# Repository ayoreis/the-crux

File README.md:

# The Crux

A minimal 3x10 ortholinear keyboard. Driven by a RP2040 with [RMK](https://rmk.rs) + [Vial](https://get.vial.today).

I've always wanted to make a keyboard, I actually started this one with much more ambitious ideas (you can find them in my earlier journals, or by going back the commit history) but realized I should start out with something simpler. So I made this! It was quite nice, and maybe I'll improve it with my previous ideas one-by-one :)

# File structure and assembly

At the top-level there's a general "bom.csv". Then the directories:

- "pcb/" contains a KiCad project and generated production files with KiCAD JLCPCB tools under "pcb/jlcpcb/".
- "case/" contains a FreeCAD file and an exported "case.step".
- "images/" contains the images above and the zine in PDF format.
- "firmware/" contains the RMK and Vial firmware. With the compiled UF2 file at "firmware/The_Crux.uf2".

The case and plate are a single piece sandwiched between the switches and PCB, so it must be fit before soldering.

---

_[Also see this project on Fallout.](https://fallout.hackclub.com/projects/4383)_

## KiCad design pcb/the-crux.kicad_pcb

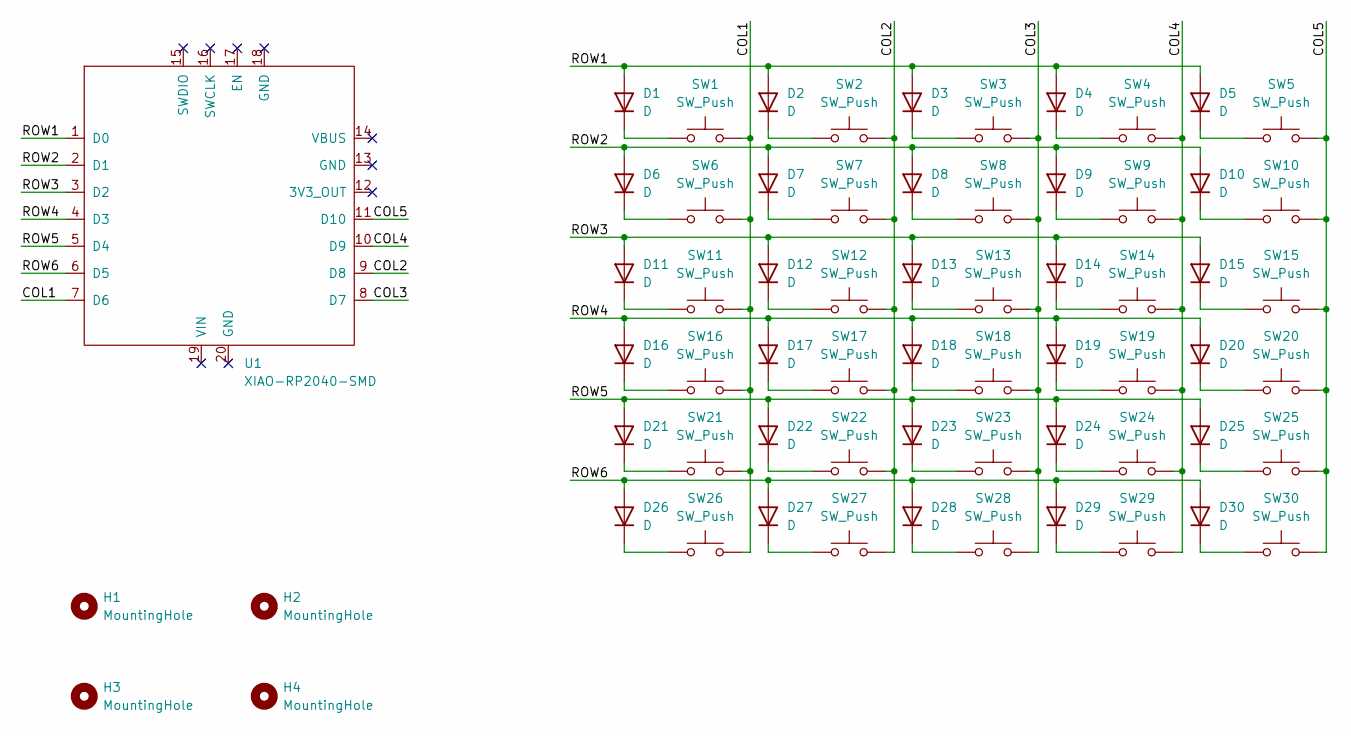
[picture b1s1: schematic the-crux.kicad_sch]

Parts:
D1, D2, D3, D4, D5, D6, D7, D8, D9, D10, D11, D12, D13, D14, D15, D16, D17, D18, D19, D20, D21, D22, D23, D24, D25, D26, D27, D28, D29, D30: D; D_DO-35_SOD27_P7.62mm_Horizontal
H1, H2, H3, H4: MountingHole; MountingHole_2.2mm_M2_Pad
SW1, SW2, SW3, SW4, SW5, SW6, SW7, SW8, SW9, SW10, SW11, SW12, SW13, SW14, SW15, SW16, SW17, SW18, SW19, SW20, SW21, SW22, SW23, SW24, SW25, SW26, SW27, SW28, SW29, SW30: SW_Push; SW_Cherry_MX_1.00u_PCB
U1: XIAO-RP2040-SMD

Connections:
/COL1: SW1.2, SW6.2, SW11.2, SW16.2, SW21.2, SW26.2, U1.7 (D6)
/COL2: SW2.2, SW7.2, SW12.2, SW17.2, SW22.2, SW27.2, U1.9 (D8)
/COL3: SW3.2, SW8.2, SW13.2, SW18.2, SW23.2, SW28.2, U1.8 (D7)
/COL4: SW4.2, SW9.2, SW14.2, SW19.2, SW24.2, SW29.2, U1.10 (D9)
/COL5: SW5.2, SW10.2, SW15.2, SW20.2, SW25.2, SW30.2, U1.11 (D10)
/ROW1: D1.2 (A), D2.2 (A), D3.2 (A), D4.2 (A), D5.2 (A), U1.1 (D0)
/ROW2: D6.2 (A), D7.2 (A), D8.2 (A), D9.2 (A), D10.2 (A), U1.2 (D1)
/ROW3: D11.2 (A), D12.2 (A), D13.2 (A), D14.2 (A), D15.2 (A), U1.3 (D2)
/ROW4: D16.2 (A), D17.2 (A), D18.2 (A), D19.2 (A), D20.2 (A), U1.4 (D3)
/ROW5: D21.2 (A), D22.2 (A), D23.2 (A), D24.2 (A), D25.2 (A), U1.5 (D4)
/ROW6: D26.2 (A), D27.2 (A), D28.2 (A), D29.2 (A), D30.2 (A), U1.6 (D5)
unnamed: D1.1 (K), SW1.1
unnamed: D2.1 (K), SW2.1
unnamed: D3.1 (K), SW3.1
unnamed: D4.1 (K), SW4.1
unnamed: D5.1 (K), SW5.1
unnamed: D6.1 (K), SW6.1
unnamed: D7.1 (K), SW7.1
unnamed: D8.1 (K), SW8.1
unnamed: D9.1 (K), SW9.1
unnamed: D10.1 (K), SW10.1
unnamed: D11.1 (K), SW11.1
unnamed: D12.1 (K), SW12.1
unnamed: D13.1 (K), SW13.1
unnamed: D14.1 (K), SW14.1
unnamed: D15.1 (K), SW15.1
unnamed: D16.1 (K), SW16.1
unnamed: D17.1 (K), SW17.1
unnamed: D18.1 (K), SW18.1
unnamed: D19.1 (K), SW19.1
unnamed: D20.1 (K), SW20.1
unnamed: D21.1 (K), SW21.1
unnamed: D22.1 (K), SW22.1
unnamed: D23.1 (K), SW23.1
unnamed: D24.1 (K), SW24.1
unnamed: D25.1 (K), SW25.1
unnamed: D26.1 (K), SW26.1
unnamed: D27.1 (K), SW27.1
unnamed: D28.1 (K), SW28.1
unnamed: D29.1 (K), SW29.1
unnamed: D30.1 (K), SW30.1

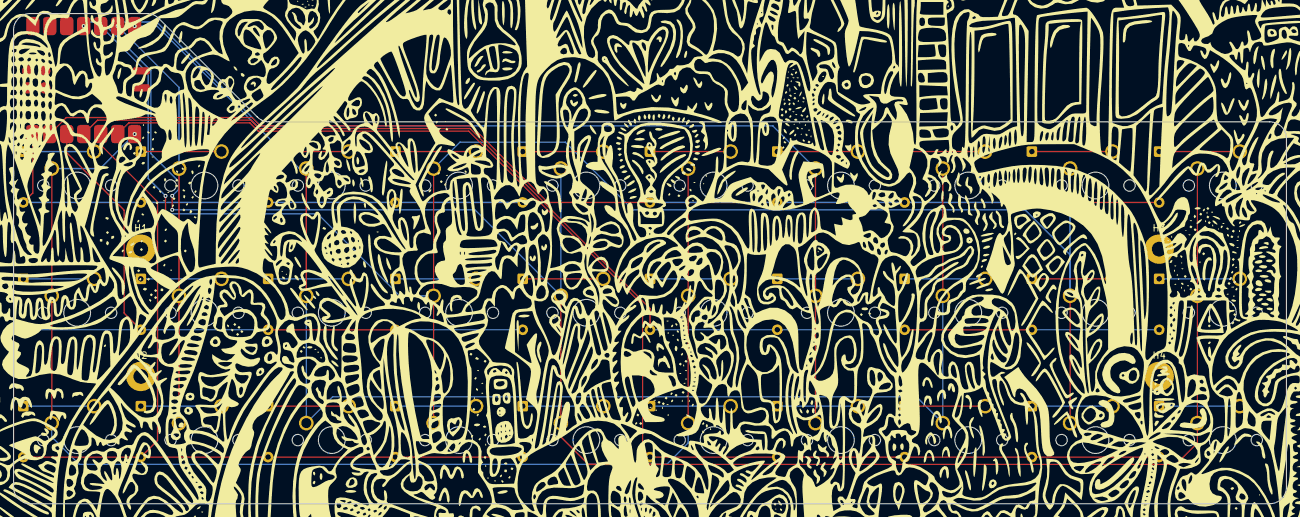
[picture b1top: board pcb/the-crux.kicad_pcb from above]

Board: 2 copper layers, 190.5 x 73.4 mm, 65 parts (0 on the bottom side), 41 nets.

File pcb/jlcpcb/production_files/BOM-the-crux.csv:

Comment,Designator,Footprint,LCSC,Quantity
XIAO-RP2040-SMD,U1,XIAO-RP2040-SMD,,1
SW_Push,SW30,SW_Cherry_MX_1.00u_PCB,,1
SW_Push,SW29,SW_Cherry_MX_1.00u_PCB,,1
SW_Push,SW28,SW_Cherry_MX_1.00u_PCB,,1
SW_Push,SW27,SW_Cherry_MX_1.00u_PCB,,1
SW_Push,SW26,SW_Cherry_MX_1.00u_PCB,,1
SW_Push,SW25,SW_Cherry_MX_1.00u_PCB,,1
SW_Push,SW24,SW_Cherry_MX_1.00u_PCB,,1
SW_Push,SW23,SW_Cherry_MX_1.00u_PCB,,1
SW_Push,SW22,SW_Cherry_MX_1.00u_PCB,,1
SW_Push,SW21,SW_Cherry_MX_1.00u_PCB,,1
SW_Push,SW20,SW_Cherry_MX_1.00u_PCB,,1
SW_Push,SW19,SW_Cherry_MX_1.00u_PCB,,1
SW_Push,SW18,SW_Cherry_MX_1.00u_PCB,,1
SW_Push,SW17,SW_Cherry_MX_1.00u_PCB,,1
SW_Push,SW16,SW_Cherry_MX_1.00u_PCB,,1
SW_Push,SW15,SW_Cherry_MX_1.00u_PCB,,1
SW_Push,SW14,SW_Cherry_MX_1.00u_PCB,,1
SW_Push,SW13,SW_Cherry_MX_1.00u_PCB,,1
SW_Push,SW12,SW_Cherry_MX_1.00u_PCB,,1
SW_Push,SW11,SW_Cherry_MX_1.00u_PCB,,1
SW_Push,SW10,SW_Cherry_MX_1.00u_PCB,,1
SW_Push,SW9,SW_Cherry_MX_1.00u_PCB,,1
SW_Push,SW8,SW_Cherry_MX_1.00u_PCB,,1
SW_Push,SW7,SW_Cherry_MX_1.00u_PCB,,1
SW_Push,SW6,SW_Cherry_MX_1.00u_PCB,,1
SW_Push,SW5,SW_Cherry_MX_1.00u_PCB,,1
SW_Push,SW4,SW_Cherry_MX_1.00u_PCB,,1
SW_Push,SW3,SW_Cherry_MX_1.00u_PCB,,1
SW_Push,SW2,SW_Cherry_MX_1.00u_PCB,,1
SW_Push,SW1,SW_Cherry_MX_1.00u_PCB,,1
D,D4,D_DO-35_SOD27_P7.62mm_Horizontal,,1
D,D11,D_DO-35_SOD27_P7.62mm_Horizontal,,1
D,D3,D_DO-35_SOD27_P7.62mm_Horizontal,,1
D,D27,D_DO-35_SOD27_P7.62mm_Horizontal,,1
D,D23,D_DO-35_SOD27_P7.62mm_Horizontal,,1
D,D30,D_DO-35_SOD27_P7.62mm_Horizontal,,1
D,D25,D_DO-35_SOD27_P7.62mm_Horizontal,,1
D,D7,D_DO-35_SOD27_P7.62mm_Horizontal,,1
D,D14,D_DO-35_SOD27_P7.62mm_Horizontal,,1
D,D2,D_DO-35_SOD27_P7.62mm_Horizontal,,1
D,D26,D_DO-35_SOD27_P7.62mm_Horizontal,,1
D,D5,D_DO-35_SOD27_P7.62mm_Horizontal,,1
D,D19,D_DO-35_SOD27_P7.62mm_Horizontal,,1
D,D8,D_DO-35_SOD27_P7.62mm_Horizontal,,1
D,D15,D_DO-35_SOD27_P7.62mm_Horizontal,,1
D,D12,D_DO-35_SOD27_P7.62mm_Horizontal,,1
D,D18,D_DO-35_SOD27_P7.62mm_Horizontal,,1
D,D10,D_DO-35_SOD27_P7.62mm_Horizontal,,1
D,D22,D_DO-35_SOD27_P7.62mm_Horizontal,,1
D,D29,D_DO-35_SOD27_P7.62mm_Horizontal,,1
D,D6,D_DO-35_SOD27_P7.62mm_Horizontal,,1
D,D24,D_DO-35_SOD27_P7.62mm_Horizontal,,1
D,D13,D_DO-35_SOD27_P7.62mm_Horizontal,,1
D,D17,D_DO-35_SOD27_P7.62mm_Horizontal,,1
D,D28,D_DO-35_SOD27_P7.62mm_Horizontal,,1
D,D1,D_DO-35_SOD27_P7.62mm_Horizontal,,1
D,D20,D_DO-35_SOD27_P7.62mm_Horizontal,,1
D,D21,D_DO-35_SOD27_P7.62mm_Horizontal,,1
D,D16,D_DO-35_SOD27_P7.62mm_Horizontal,,1
D,D9,D_DO-35_SOD27_P7.62mm_Horizontal,,1

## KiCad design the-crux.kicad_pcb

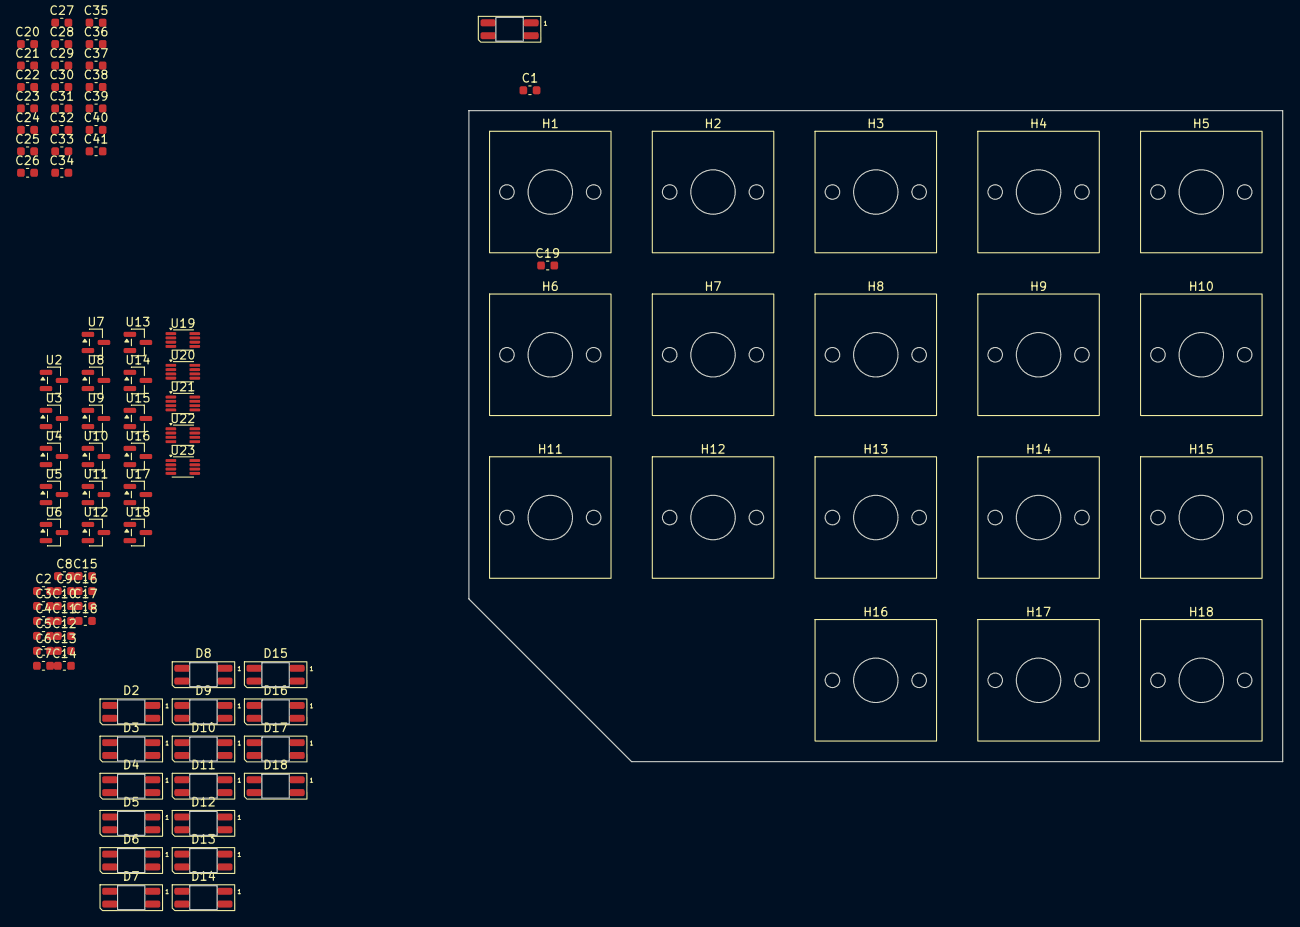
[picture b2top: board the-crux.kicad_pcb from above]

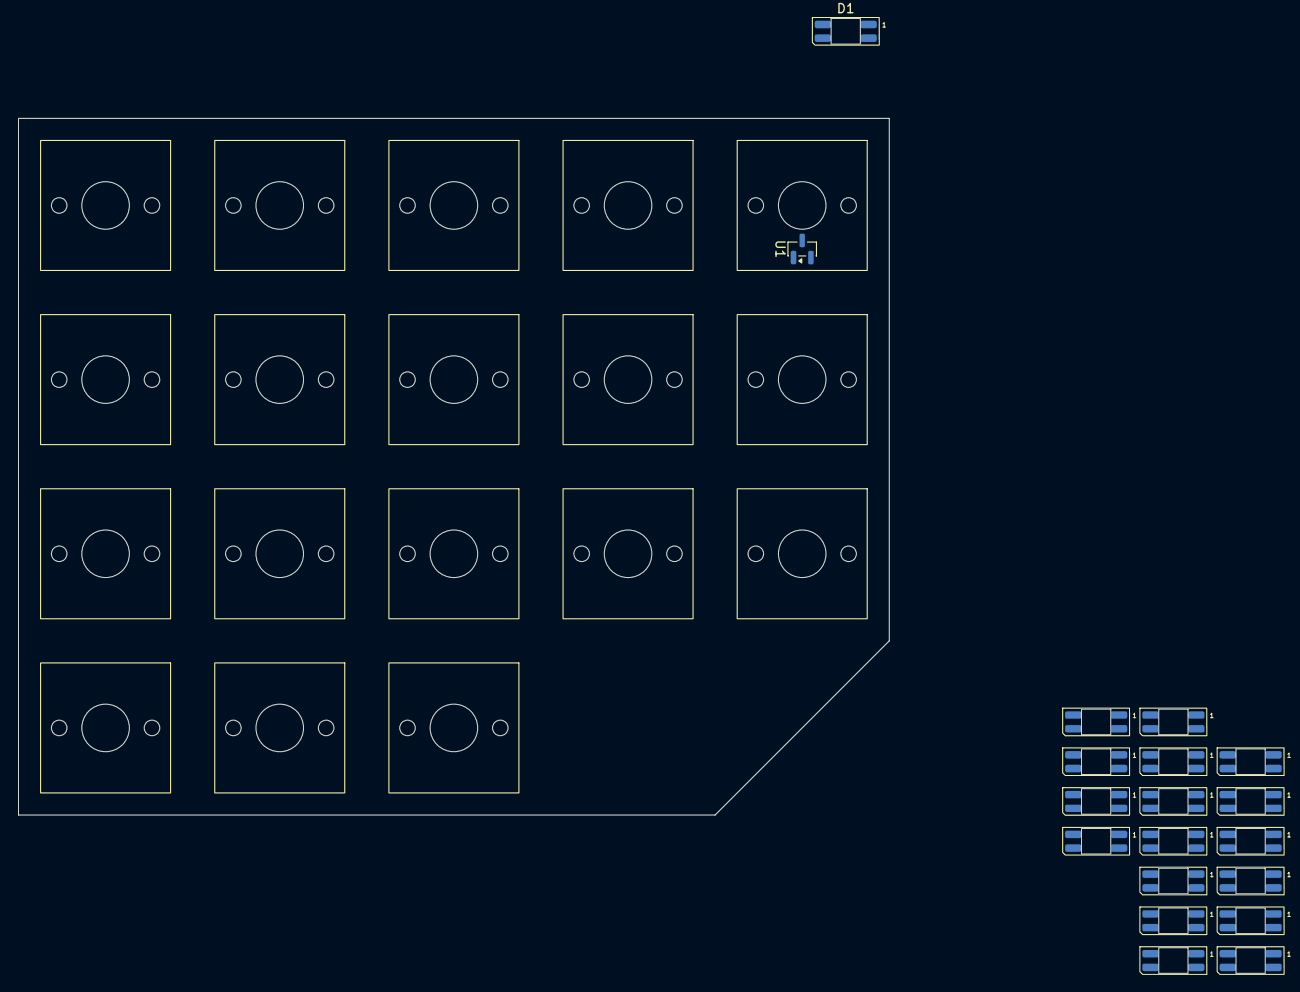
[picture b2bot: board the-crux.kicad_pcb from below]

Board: 2 copper layers, 100 parts (2 on the bottom side), 34 nets, no tracks yet.

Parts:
C1, C2, C3, C4, C5, C6, C7, C8, C9, C10, C11, C12, C13, C14, C15, C16, C17, C18, C19, C20, C21, C22, C23, C24, C25, C26, C27, C28, C29, C30, C31, C32, C33, C34, C35, C36, C37, C38, C39, C40, C41: 0.1uF; C_0603_1608Metric
D1, D2, D3, D4, D5, D6, D7, D8, D9, D10, D11, D12, D13, D14, D15, D16, D17, D18: SK6812MINI-E; LED_SK6812MINI-E_PLCC4_3.2x2.8mm_P1.5mm_Reversible
H1, H2, H3, H4, H5, H6, H7, H8, H9, H10, H11, H12, H13, H14, H15, H16, H17, H18: MountingHole; SW_GATERON_LowProfileMagnetic_Reversible
U1, U2, U3, U4, U5, U6, U7, U8, U9, U10, U11, U12, U13, U14, U15, U16, U17, U18: DRV5056A3xDBZ; SOT-23
U19, U20, U21, U22, U23: TS5A3359DCU; VSSOP-8_2.3x2mm_P0.5mm

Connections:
+5V: C1.1, C2.1, C3.1, C4.1, C5.1, C6.1, C7.1, C8.1, C9.1, C10.1, C11.1, C12.1, C13.1, C14.1, C15.1, C16.1, C17.1, C18.1, C19.1, C20.1, C21.1, C22.1, C23.1, C24.1, C25.1, C26.1, C27.1, C28.1, C29.1, C30.1, C31.1, C32.1, C33.1, C34.1, C35.1, C36.1, C37.1, C38.1, C39.1, C40.1, C41.1, D1.1 (VDD), D2.1 (VDD), D3.1 (VDD), D4.1 (VDD), D5.1 (VDD), D6.1 (VDD), D7.1 (VDD), D8.1 (VDD), D9.1 (VDD), D10.1 (VDD), D11.1 (VDD), D12.1 (VDD), D13.1 (VDD), D14.1 (VDD), D15.1 (VDD), D16.1 (VDD), D17.1 (VDD), D18.1 (VDD), U1.1 (VCC), U2.1 (VCC), U3.1 (VCC), U4.1 (VCC), U5.1 (VCC), U6.1 (VCC), U7.1 (VCC), U8.1 (VCC), U9.1 (VCC), U10.1 (VCC), U11.1 (VCC), U12.1 (VCC), U13.1 (VCC), U14.1 (VCC), U15.1 (VCC), U16.1 (VCC), U17.1 (VCC), U18.1 (VCC), U19.8 (VCC), U20.8 (VCC), U21.8 (VCC), U22.8 (VCC), U23.8 (VCC)
/Linear Hall-Effect Sensors/OUT_1: U1.2 (OUT), U19.1 (NO0)
/Linear Hall-Effect Sensors/OUT_2: U2.2 (OUT), U19.2 (NO1)
/Linear Hall-Effect Sensors/OUT_3: U3.2 (OUT), U19.3 (NO2)
/Linear Hall-Effect Sensors/OUT_4: U4.2 (OUT), U20.1 (NO0)
/Linear Hall-Effect Sensors/OUT_5: U5.2 (OUT), U20.2 (NO1)
/Linear Hall-Effect Sensors/OUT_6: U6.2 (OUT), U20.3 (NO2)
/Linear Hall-Effect Sensors/OUT_7: U7.2 (OUT), U21.1 (NO0)
/Linear Hall-Effect Sensors/OUT_8: U8.2 (OUT), U21.2 (NO1)
/Linear Hall-Effect Sensors/OUT_9: U9.2 (OUT), U21.3 (NO2)
/Linear Hall-Effect Sensors/OUT_10: U10.2 (OUT), U22.1 (NO0)
/Linear Hall-Effect Sensors/OUT_11: U11.2 (OUT), U22.2 (NO1)
/Linear Hall-Effect Sensors/OUT_12: U12.2 (OUT), U22.3 (NO2)
/Linear Hall-Effect Sensors/OUT_13: U13.2 (OUT), U23.1 (NO0)
/Linear Hall-Effect Sensors/OUT_14: U14.2 (OUT), U23.2 (NO1)
/Linear Hall-Effect Sensors/OUT_15: U15.2 (OUT), U23.3 (NO2)
GND: C1.2, C2.2, C3.2, C4.2, C5.2, C6.2, C7.2, C8.2, C9.2, C10.2, C11.2, C12.2, C13.2, C14.2, C15.2, C16.2, C17.2, C18.2, C19.2, C20.2, C21.2, C22.2, C23.2, C24.2, C25.2, C26.2, C27.2, C28.2, C29.2, C30.2, C31.2, C32.2, C33.2, C34.2, C35.2, C36.2, C37.2, C38.2, C39.2, C40.2, C41.2, D1.3 (GND), D2.3 (GND), D3.3 (GND), D4.3 (GND), D5.3 (GND), D6.3 (GND), D7.3 (GND), D8.3 (GND), D9.3 (GND), D10.3 (GND), D11.3 (GND), D12.3 (GND), D13.3 (GND), D14.3 (GND), D15.3 (GND), D16.3 (GND), D17.3 (GND), D18.3 (GND), U1.3 (GND), U2.3 (GND), U3.3 (GND), U4.3 (GND), U5.3 (GND), U6.3 (GND), U7.3 (GND), U8.3 (GND), U9.3 (GND), U10.3 (GND), U11.3 (GND), U12.3 (GND), U13.3 (GND), U14.3 (GND), U15.3 (GND), U16.3 (GND), U17.3 (GND), U18.3 (GND), U19.4 (GND), U20.4 (GND), U21.4 (GND), U22.4 (GND), U23.4 (GND)
unnamed: D1.2 (DOUT), D2.4 (DIN)
unnamed: D2.2 (DOUT), D3.4 (DIN)
unnamed: D3.2 (DOUT), D4.4 (DIN)
unnamed: D4.2 (DOUT), D5.4 (DIN)
unnamed: D5.2 (DOUT), D6.4 (DIN)
unnamed: D6.2 (DOUT), D7.4 (DIN)
unnamed: D7.2 (DOUT), D8.4 (DIN)
unnamed: D8.2 (DOUT), D9.4 (DIN)
unnamed: D9.2 (DOUT), D10.4 (DIN)
unnamed: D10.2 (DOUT), D11.4 (DIN)
unnamed: D11.2 (DOUT), D12.4 (DIN)
unnamed: D12.2 (DOUT), D13.4 (DIN)
unnamed: D13.2 (DOUT), D14.4 (DIN)
unnamed: D14.2 (DOUT), D15.4 (DIN)
unnamed: D15.2 (DOUT), D16.4 (DIN)
unnamed: D16.2 (DOUT), D17.4 (DIN)
unnamed: D17.2 (DOUT), D18.4 (DIN)

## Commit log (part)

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2025-12-31 Initialise project
2026-01-06 Name project and add README
2026-01-07 Design symbols for DRV5056 and SK6812MINI-E
2026-01-09 Add component links and datasheets
2026-01-09 Ignore #auto_saved_files#
2026-01-09 Wire LEDs
2026-01-11 Design symbol for TS5A3359
2026-01-11 Wire linear hall-effect sensors and analog multiplexers
2026-01-19 Configure formatting
2026-01-19 Design footprint for GATERON Low Profile Magnetic switch
2026-01-19 Wire switches
2026-01-19 Design footprint for SK6812MINI-E
2026-01-20 Fix symbols and footprints
